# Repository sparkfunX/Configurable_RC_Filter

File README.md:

SparkX Configurable RC Filter
===================================================================

[*SparkX Configurable RC Filter (SPX-16392)*](https://www.sparkfun.com/products/16392)

A DIP selectable RC Filter.

Repository Contents
-------------------

* **/Documents** - Contains schematic .pdf
* **/Hardware** - Current .brd and .sch files for product

License Information
-------------------

This product is _**open source**_!

Please review the LICENSE.md file for license information.

If you have any questions or concerns on licensing, please contact technical support on our [SparkFun forums] (https://forum.sparkfun.com/viewforum.php?f=152).

Distributed as-is; no warranty is given.

- Your friends at SparkFun.

_<COLLABORATION CREDIT>_

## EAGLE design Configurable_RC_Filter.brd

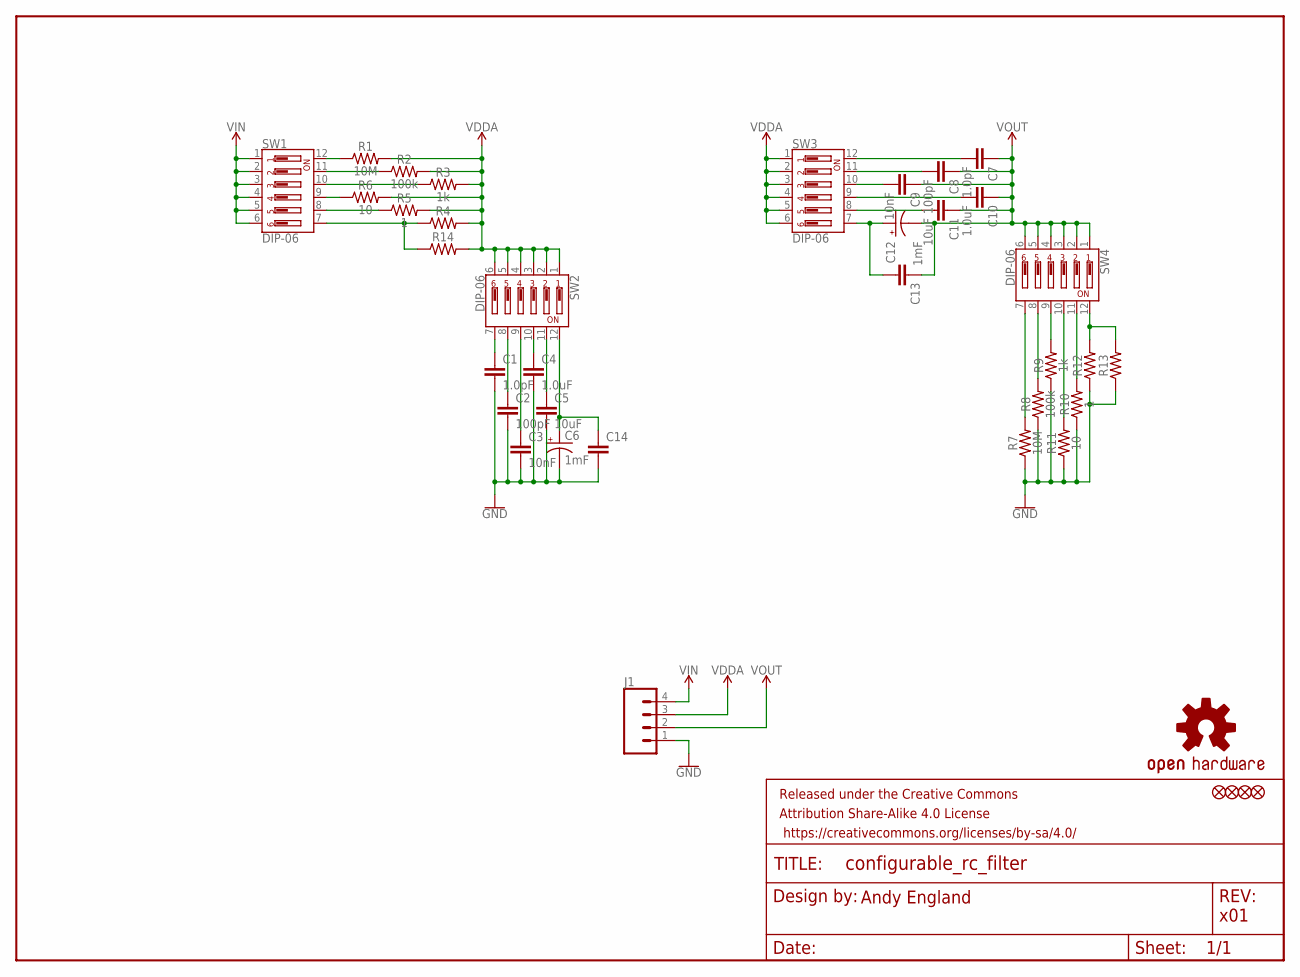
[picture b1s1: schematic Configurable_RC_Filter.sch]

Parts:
C1, C7: 1.0pF; 0603
C2, C8: 100pF; 0603
C3, C9: 10nF; 0603
C4, C10: 1.0uF; 0603
C5, C11: 10uF; 0603
C6, C12: 1mF; CPOL-RADIAL-5MM-10MM
C13, C14: CAP-0603; 0603
FD1, FD2, FD3, FD4: FIDUCIAL1X2; FIDUCIAL-1X2
FRAME1: FRAME-LETTER; CREATIVE_COMMONS
J1: CONN_041X04_NO_SILK; 1X04_NO_SILK
LOGO1: OSHW-LOGOS; OSHW-LOGO-S
R1, R7: 10M; 0603
R2, R8: 100k; 0603
R3, R9: 1k; 0603
R4, R12: AXIAL-0.3
R5, R10: 1; 0603
R6, R11: 10; 0603
R13, R14: 0603
SW1, SW2, SW3, SW4: DIP-06; DIPSWITCH-06-SMD

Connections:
GND: C1.2, C2.2, C3.2, C4.2, C5.2, C6.-, C14.2, J1.1, R7.1, R8.1, R9.1, R10.1, R11.1, R12.P$1 (1), R13.1
unnamed: R1.1, SW1.12
unnamed: R2.1, SW1.11
unnamed: C1.1, SW2.7
unnamed: R3.1, SW1.10
unnamed: R6.1, SW1.9
unnamed: R5.1, SW1.8
unnamed: R4.P$1 (1), R14.1, SW1.7
unnamed: C2.1, SW2.8
unnamed: C3.1, SW2.9
unnamed: C4.1, SW2.10
unnamed: C5.1, SW2.11
unnamed: C6.+, C14.1, SW2.12
unnamed: C12.+, C13.2, SW3.7
unnamed: C11.2, SW3.8
unnamed: C10.2, SW3.9
unnamed: C9.2, SW3.10
unnamed: C8.2, SW3.11
unnamed: C7.2, SW3.12
unnamed: R7.2, SW4.7
unnamed: R8.2, SW4.8
unnamed: R9.2, SW4.9
unnamed: R12.P$2 (2), R13.2, SW4.12
unnamed: R10.2, SW4.11
unnamed: R11.2, SW4.10
VDDA: J1.3, R1.2, R2.2, R3.2, R4.P$2 (2), R5.2, R6.2, R14.2, SW2.1, SW2.2, SW2.3, SW2.4, SW2.5, SW2.6, SW3.1, SW3.2, SW3.3, SW3.4, SW3.5, SW3.6
VIN: J1.4, SW1.1, SW1.2, SW1.3, SW1.4, SW1.5, SW1.6
VOUT: C7.1, C8.1, C9.1, C10.1, C11.1, C12.-, C13.1, J1.2, SW4.1, SW4.2, SW4.3, SW4.4, SW4.5, SW4.6

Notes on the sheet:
Andy England
x01

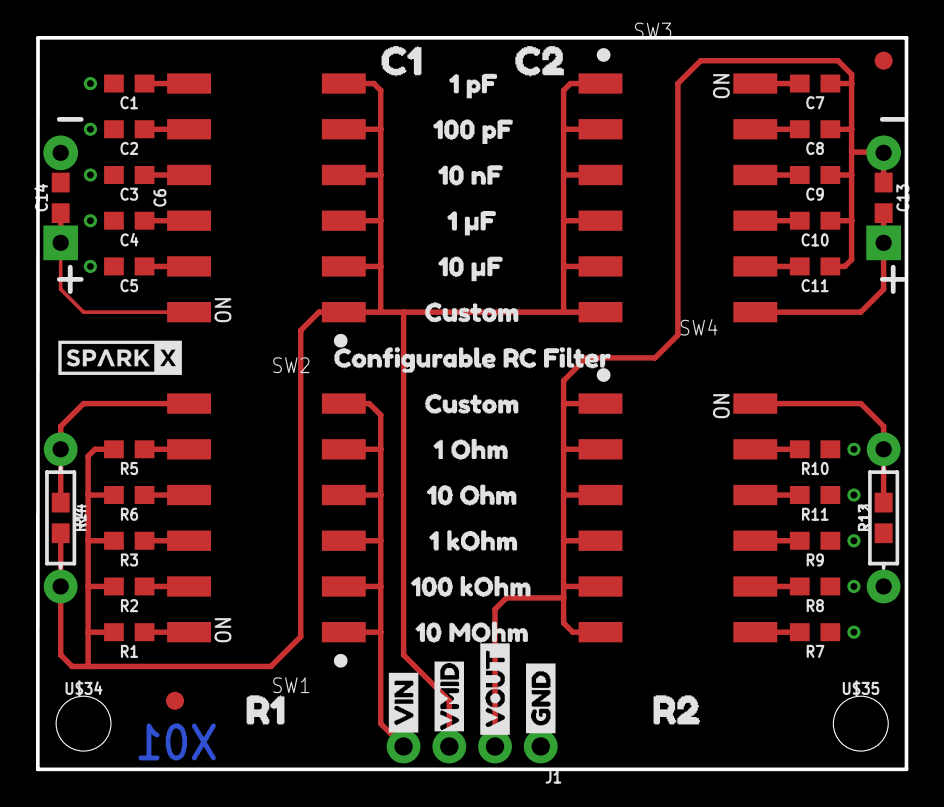
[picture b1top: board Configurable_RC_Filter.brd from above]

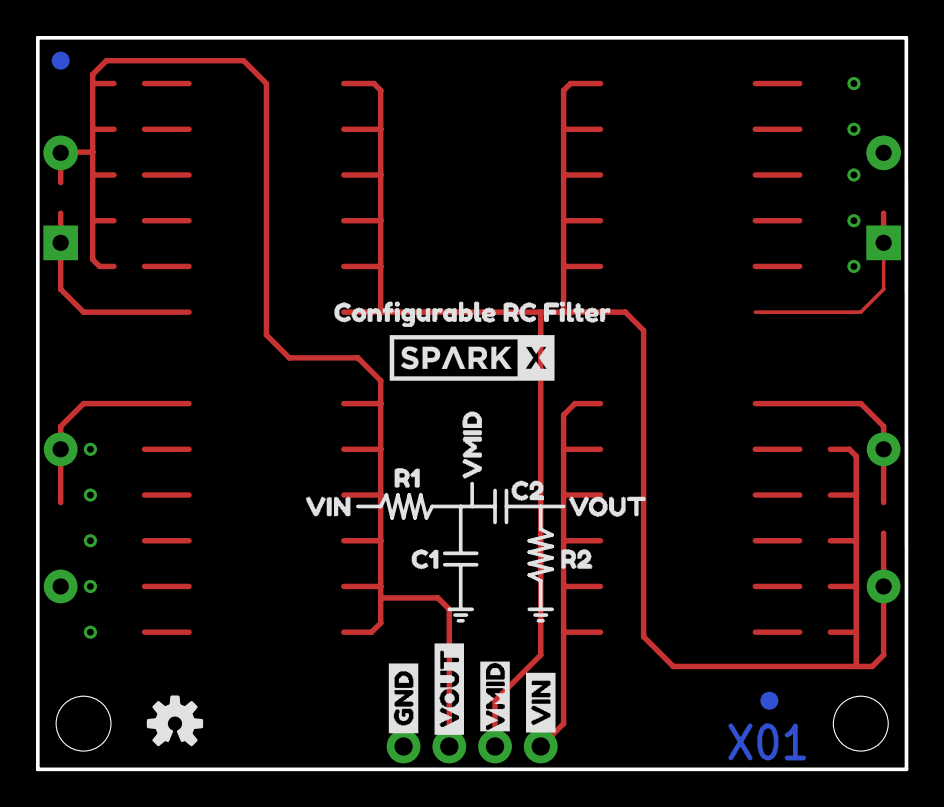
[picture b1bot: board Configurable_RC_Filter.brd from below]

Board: 2 copper layers, 48.3 x 40.6 mm, 76 parts (16 on the bottom side), 28 nets.

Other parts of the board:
U$1: 1_#F9
U$2: 1_KOHM7
U$3: 10_#F8
U$4: 10_MOHM6
U$5, U$6: GND0
U$7, U$8: VIN1
U$9, U$10: VMID3
U$11, U$12: VOUT3
U$13: 10_NF11
U$14: 10_OHM4
U$15: 100_KOHM10
U$16: C10
U$17: C21
U$18, U$27: R12
U$19, U$28: R23
U$20: _1_OHM5
U$21: _1_PF13
U$22: _100_PF12
U$23, U$24: CUSTOM3
U$25: C11
U$26: C20
U$29: VIN4
U$30: VMID5
U$31: VOUT6
U$32, U$33: CONFIGURABLE_RC_FILTER0
U$34, U$35: STAND-OFF-TIGHT
U$36: SPARKX-SMALL
U$37: SPARKX-MEDIUM

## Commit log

2020-01-31 Change cap to NS package.
2020-02-19 Add panel
2020-03-04 Reorganizing file structure
    Created hardware and documents folders. Also generated .pdf of schematic and .zip of eagle files.
2020-03-04 Updated readme image

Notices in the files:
parts and their libraries:
SparkFun-Aesthetics: Licensing: Creative Commons ShareAlike 4.0 International - https://creativecommons.org/licenses/by-sa/4.0
SparkFun-Aesthetics: Released under the Creative Commons Attribution Share-Alike 4.0 License
SparkFun-Aesthetics: https://creativecommons.org/licenses/by-sa/4.0
